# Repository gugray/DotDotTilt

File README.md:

# Dot-Dot-Tilt!

_Matrix display meets motion sensor for fun inertial games_

This repository contains the source code, schematic, PCB and other design files for Dot-Dot-Tilt!, a small motion-controlled device for inertial simulations and games.

Check out the project's Hackaday page at [hackaday.io/project/186687-dot-dot-tilt](https://hackaday.io/project/186687-dot-dot-tilt), or the short video showing it [in action](https://youtu.be/RH-mNLPE31o).

Here's what it looks like from the front, showing a 3D cube that rotates in reaction to tilting:

And here's the back view, with the electronics inside:

## Building the code

In order to build the C++ source code you need VS Code with the PlatformIO plugin installed. The code here targets the SAMD21 microcontroller, and specifically, the Seeeduino XIAO board.

## License

Everything in this repository, with the exception of the files under `code/lib`, are (C) Gabor L Ugray. All code is released under the MIT license, and all other content is released under Creative Commons CC-BY-SA-NC. The files under `code/lib` are included under their respective licenses, as specified in the source files.

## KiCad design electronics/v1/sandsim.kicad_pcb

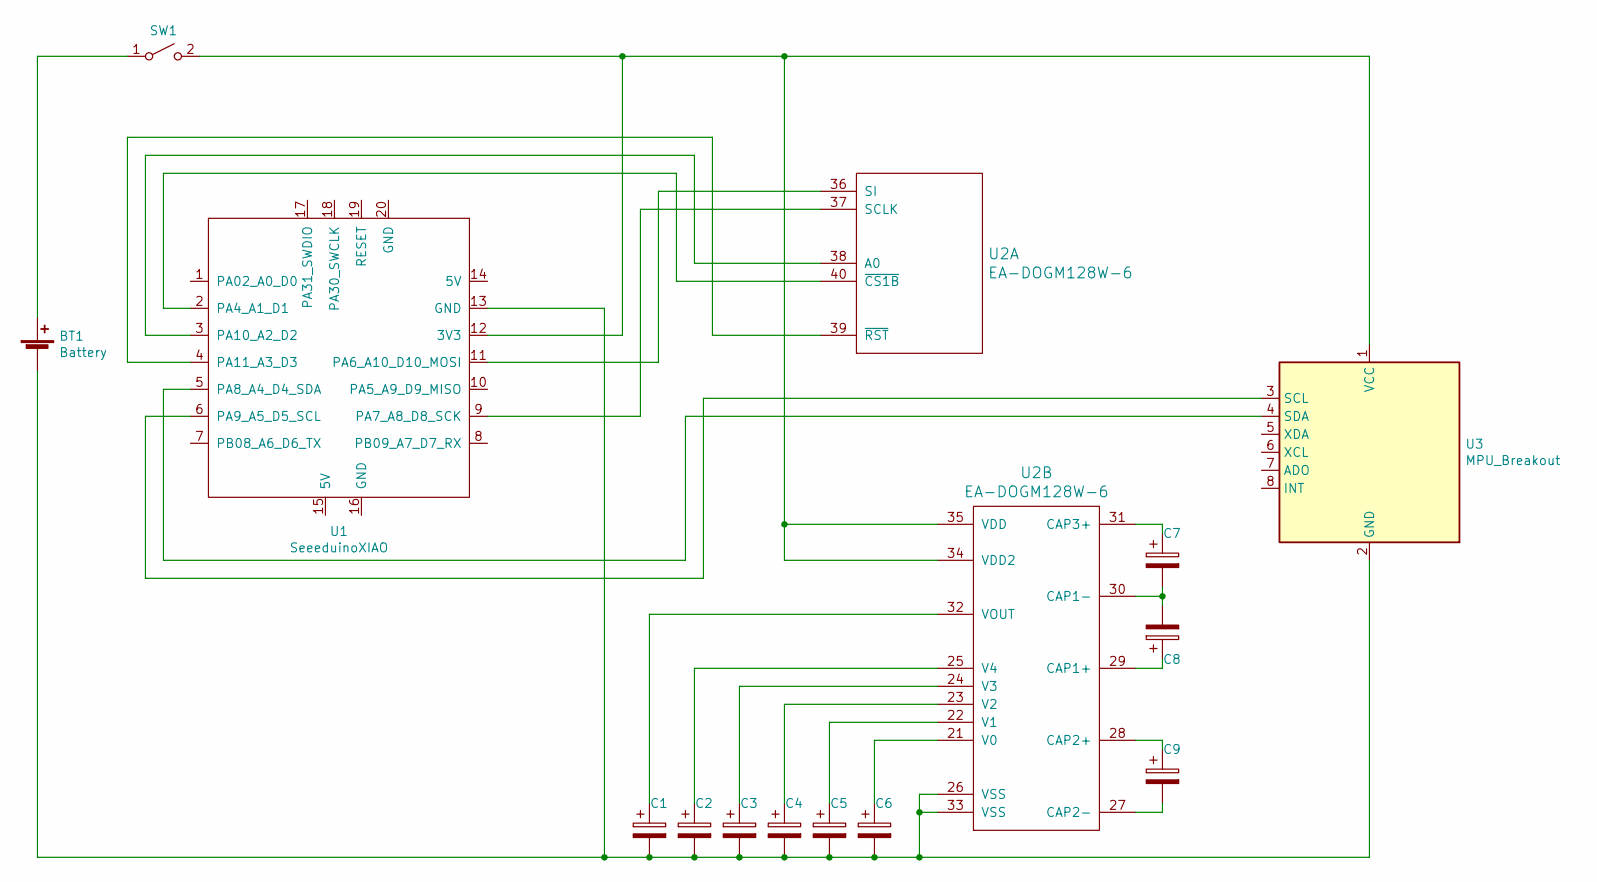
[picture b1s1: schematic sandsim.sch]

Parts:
BT1: Battery; Battery_CR2032
C1, C2, C3, C4, C5, C6, C7, C8, C9: CP; CP_Radial_D5.0mm_L10mm_P2.50mm_Lying
SW1: SW_SPST; SolderWire-0.25sqmm_1x02_P4.5mm_D0.65mm_OD2mm
U1: SeeeduinoXIAO; XIAO-MOUDLE14P-2.54-21X17.8MM_Pins
U2: EA-DOGM128W-6; EA_DOGM128-6
U3: MPU_Breakout

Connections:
unnamed: BT1.1 (+), SW1.1 (A)
unnamed: BT1.2 (-), C1.2, C2.2, C3.2, C4.2, C5.2, C6.2, U1.13 (GND), U2.26 (VSS), U2.33 (VSS), U3.2 (GND)
unnamed: C1.1, U2.32 (VOUT)
unnamed: C2.1, U2.25 (V4)
unnamed: C3.1, U2.24 (V3)
unnamed: C4.1, U2.23 (V2)
unnamed: C5.1, U2.22 (V1)
unnamed: C6.1, U2.21 (V0)
unnamed: C7.1, U2.31 (CAP3+)
unnamed: C7.2, C8.2, U2.30 (CAP1-)
unnamed: C8.1, U2.29 (CAP1+)
unnamed: C9.1, U2.28 (CAP2+)
unnamed: C9.2, U2.27 (CAP2-)
unnamed: SW1.2 (B), U1.12 (3V3), U2.34 (VDD2), U2.35 (VDD), U3.1 (VCC)
unnamed: U1.2 (PA4_A1_D1), U2.40 (~CS1B)
unnamed: U1.3 (PA10_A2_D2), U2.38 (A0)
unnamed: U1.4 (PA11_A3_D3), U2.39 (~RST)
unnamed: U1.5 (PA8_A4_D4_SDA), U3.4 (SDA)
unnamed: U1.6 (PA9_A5_D5_SCL), U3.3 (SCL)
unnamed: U1.9 (PA7_A8_D8_SCK), U2.37 (SCLK)
unnamed: U1.11 (PA6_A10_D10_MOSI), U2.36 (SI)

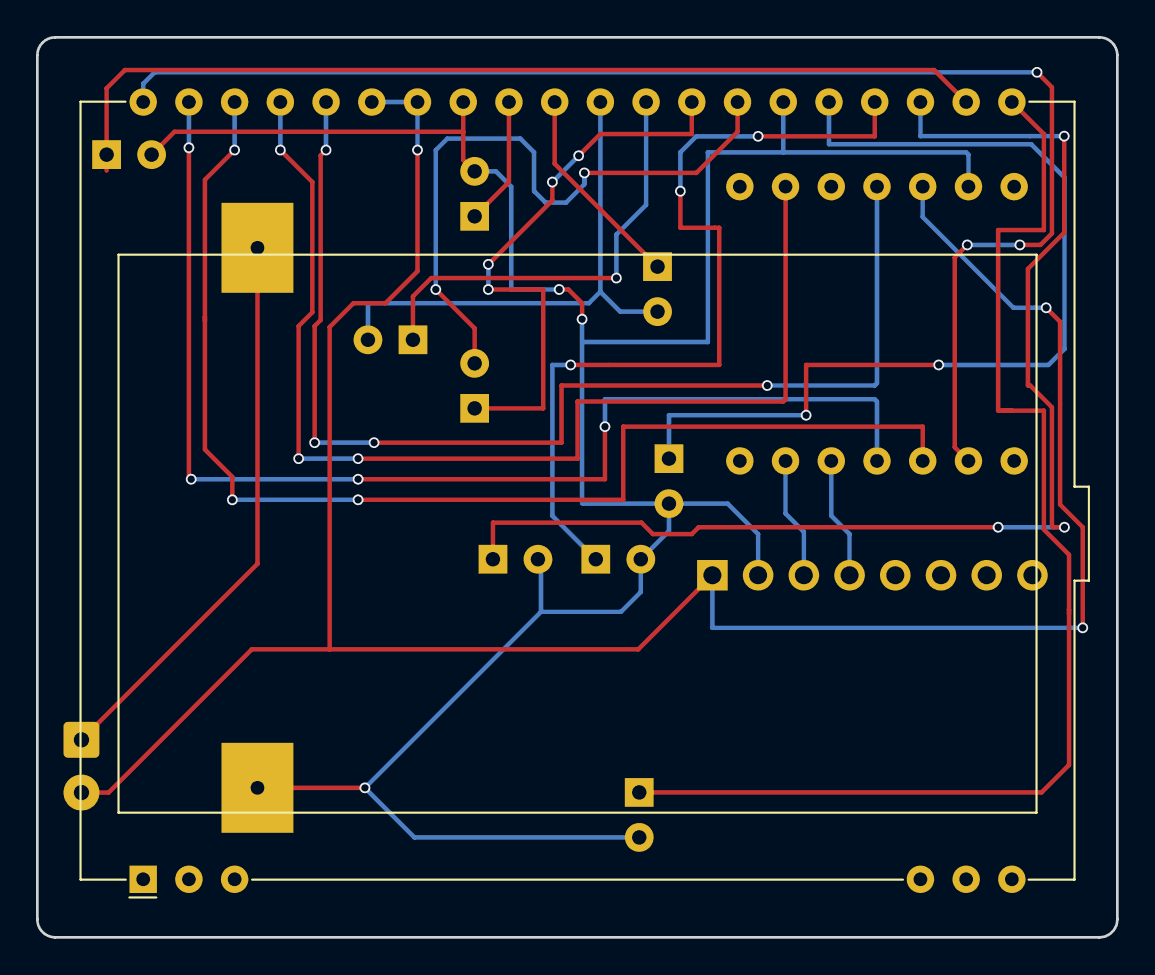
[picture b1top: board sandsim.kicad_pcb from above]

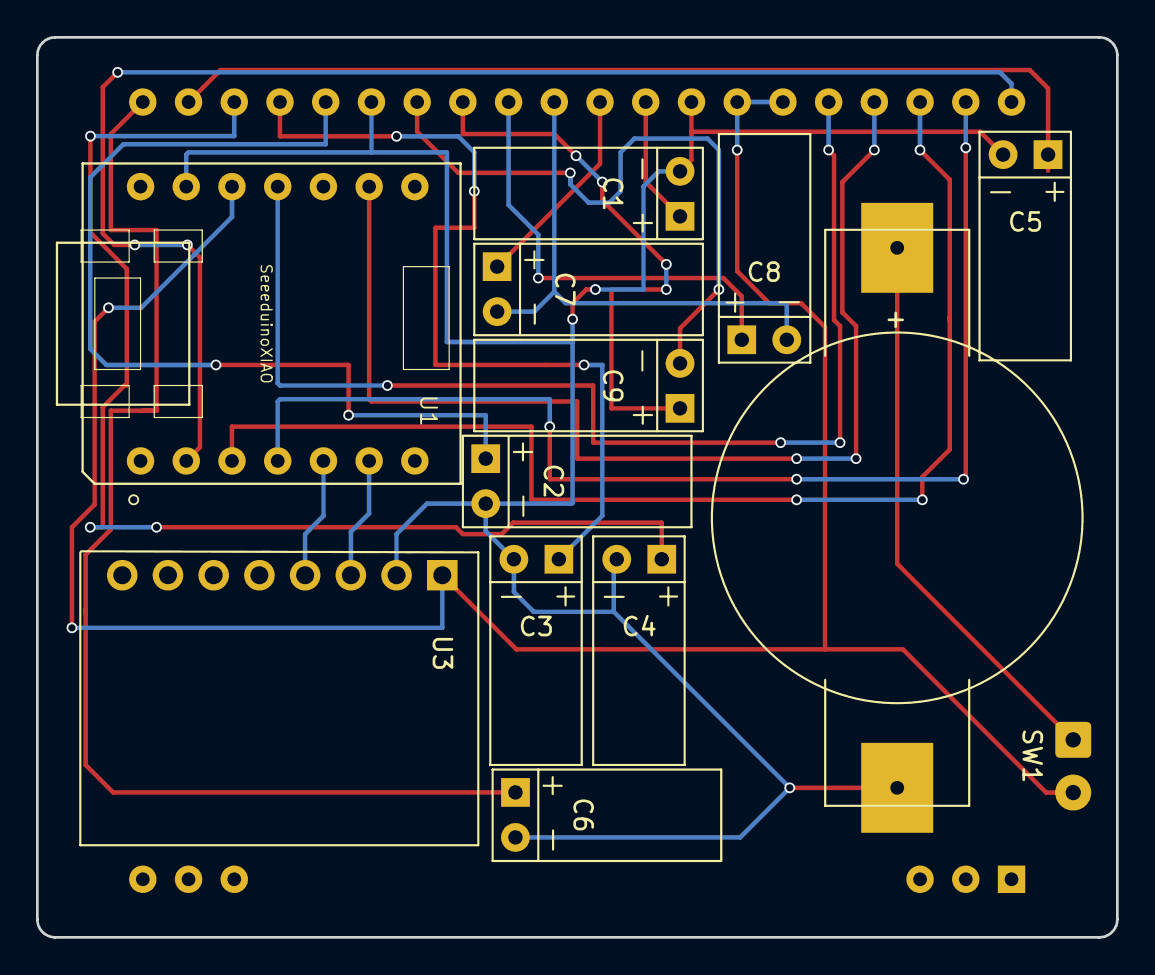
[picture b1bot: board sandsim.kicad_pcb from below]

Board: 2 copper layers, 60.0 x 50.0 mm, 14 parts (13 on the bottom side), 21 nets.

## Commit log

2022-07-08 curated fortunes
2022-07-09 DOGM128 display works
2022-07-09 sand simulation and MPU6050 sensing WIP
2022-07-10 works with MPU! (unoptimized)
2022-07-10 optimized: 2048 grains!
2022-07-15 power saving display refresh: only write on change
2022-08-01 designed board; got working on board; refact for multiple programs
2022-08-01 fix: unneeded files deleted
2022-08-01 refact: canvas
2022-08-02 rotating cube program
2022-08-04 we got a menu (with left/right flip gesture)
2022-08-05 update for publishing on hackaday
2022-08-05 added readme with license
2022-08-05 README update
